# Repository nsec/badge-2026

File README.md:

# NorthSec Badge 2026 Firmware (ESP32-S3)

Bare-bones firmware scaffold for the **NorthSec 2026 CTF badge**, targeting **ESP32-S3**.

Design goals (repo requirements):

- **Arduino framework**, but **no `.ino`** (pure C++ entrypoint)
- **PlatformIO-based** build (produces flashable `.bin` outputs)
- **Two concurrent firmware images** via partitions: **`conference`** and **`ctf`**
- A simple **serial CLI**, including a command to **switch which firmware boots next**
- Clear hierarchy separating:
  - `lib/core/` → hardware/system modules
  - `lib/challenges/` → CTF challenge modules
- GitHub Actions workflow builds on PR/push to `main`, and **publishes artifacts on version tags**

## Repo layout

```
src/
  main.cpp                     C++ Arduino entrypoint (no .ino)

lib/
  core/
    cli/                        Serial command line
    system/                     OTA boot selection / dual-firmware helpers
    hardware/                   Hardware abstraction (pins, drivers)
  challenges/
    registry.*                  Challenge init/tick hooks
    example_challenge.*         Placeholder challenge module

partitions/
  badge_factory_ota.csv         Partition table (conference + ctf)

.github/workflows/
  build.yml                     CI build + tag-based release

platformio.ini                  PlatformIO project config
```

## PlatformIO + Arduino (no .ino)

This project uses PlatformIO with the Arduino framework.
The entrypoint is `src/main.cpp` (standard Arduino `setup()` / `loop()`), not a `.ino`.

## Dual firmware: `conference` + `ctf`

The partition table `partitions/badge_factory_ota.csv` defines:

- `conference` (app) — a "golden" image
- `ctf` (app) — an alternate/updated image
- `otadata` (data) — controls which app partition boots next

### How switching works

Under Arduino-ESP32, you can call ESP-IDF’s OTA APIs. This repo wraps them in:

- `lib/core/system/ota_manager.*`

That module provides:

- `core::ota::printBootInfo(Stream&)`
- `core::ota::setNextBoot(BootTarget, Stream&)`

## Serial CLI

The CLI is implemented in `lib/core/cli/` and runs over `Serial` at **115200**.

Commands:

- `help`
- `info` — print running partition and configured boot partition
- `boot conference` — set *next boot* to `conference` and reboot
- `boot ctf` — set *next boot* to `ctf` and reboot
- `reboot`

## Building locally

### Prerequisites

- **VS Code** with **PlatformIO IDE extension** installed, **OR**
- **PlatformIO Core** (CLI) installed

### Windows Setup (Important!)

**This project uses ESP-IDF framework to avoid Windows path-length issues with Arduino-ESP32 SDK extraction.**

Before building, set a short PlatformIO core directory to prevent path issues:

```powershell
# Set environment variable permanently (restart VS Code after)
setx PLATFORMIO_CORE_DIR C:\pio
```

Then **restart VS Code** or your terminal.

### First-Time Setup

1. Clone this repository:
   ```powershell
   git clone https://github.com/yourusername/badge-2026.git
   cd badge-2026
   ```

2. Set the short core directory (Windows only, see above)

3. Open the project in VS Code with PlatformIO extension, or use CLI

### Build

**In VS Code:** Click the PlatformIO "Build" button (checkmark icon) in the bottom toolbar

**Or via CLI:**
```powershell
# Build for conference partition (default)
C:\pio\penv\Scripts\platformio.exe run -e esp32-s3-devkitc-1-conference

# Or if platformio is in PATH
pio run
```

First build will download Arduino-ESP32 framework and toolchains. Subsequent builds are much faster.

### Dual Firmware Build

The badge uses a **conference + CTF** partition layout for dual-firmware boot:

- **conference** partition (`0x10000`) - Conference/stable image
- **ctf** partition (`0x150000`) - CTF challenges image

**To flash both partitions:**

```powershell
# 1. Upload to conference partition
C:\pio\penv\Scripts\platformio.exe run -e esp32-s3-devkitc-1-conference -t upload

# 2. Upload the CTF firmware to ctf partition
C:\pio\penv\Scripts\platformio.exe run -e esp32-s3-devkitc-1-ctf -t upload
```

**In VS Code:** Use the environment switcher in the bottom toolbar to select `esp32-s3-devkitc-1-conference` or `esp32-s3-devkitc-1-ctf`, then click Upload.

After flashing both, you can use the badge CLI commands to switch between them:
- `boot conference` - Set next boot to conference partition
- `boot ctf` - Set next boot to ctf partition
- `info` - Show current boot partition

Build outputs (including flashable binaries) appear under:

- `.pio/build/<env>/firmware.bin`
- `.pio/build/<env>/bootloader.bin`
- `.pio/build/<env>/partitions.bin`

### Flash

If you have a board connected and the correct upload port set:

```powershell
pio run -t upload
```

### Monitor

```powershell
pio device monitor
```

## Native Simulator

A desktop simulator allows running the badge firmware on your development machine
without hardware. Useful for testing CLI commands, debugging, and development.

### Prerequisites

- PlatformIO Core (CLI)
- GCC with C++17 and pthread support (Linux/macOS)
- For Windows: WSL recommended

### First-Time Setup

Initialize the FreeRTOS submodule:

```bash
git submodule update --init --recursive
```

### Build

```bash
pio run -e native
```

### Run

```bash
./.pio/build/native/program
```

The simulator presents the same CLI as the real badge. Press `Ctrl+C` to exit.

## CI/CD - GitHub Actions Workflow

### Automated Builds

The workflow in `.github/workflows/build.yml` automatically builds firmware on:

- **Pull Requests** targeting `main` - Build verification
- **Push to `main`** - Build and upload artifacts
- **Version Tags** (`v*`) - Build, create GitHub Release with binaries

### What Gets Built

Both firmware variants are built in parallel:
- **Conference firmware** (`badge-conference.bin`) - Conference mode with schedule and social features
- **CTF firmware** (`badge-ctf.bin`) - CTF challenges mode
- Supporting files: `bootloader.bin`, `partitions.bin`

### Creating a Release

**Step 1: Open a Pull Request**
```bash
git checkout -b feature-my-changes
# Make your changes
git add .
git commit -m "Add new feature"
git push origin feature-my-changes
```
Open PR on GitHub targeting `main` branch. GitHub Actions will build and verify.

**Step 2: Merge to Main**
After review, merge the PR. This triggers a build and uploads artifacts.

**Step 3: Create a Release Tag**
```bash
# Pull latest main
git checkout main
git pull origin main

# Create and push version tag
git tag v1.0.0
git push origin v1.0.0
```

Or use GitHub's web interface:
1. Go to repository → Releases → "Create a new release"
2. Click "Choose a tag" → Type new tag (e.g., `v1.0.0`) → "Create new tag"
3. Set release title (e.g., "NorthSec Badge 2026 v1.0.0")
4. GitHub Actions will automatically build and attach binaries

### Release Artifacts

Each release includes:
- `badge-conference.bin` - Conference firmware for conference partition
- `badge-ctf.bin` - CTF challenges firmware for CTF partition
- `bootloader.bin` - ESP32-S3 bootloader
- `partitions.bin` - Partition table
- `FLASH_INSTRUCTIONS.txt` - Complete flashing guide

## Flashing Pre-Built Firmware

### Prerequisites

Install esptool:
```bash
pip install esptool
```

Find your serial port:
- **Windows**: Check Device Manager → Ports (COM & LPT) → Look for "USB Serial Device" (e.g., COM4)
- **Linux**: `ls /dev/ttyACM* /dev/ttyUSB*` (usually /dev/ttyACM0)
- **Mac**: `ls /dev/cu.*` (look for cu.usbmodem*)

### Download Release Files

Go to [Releases](https://github.com/yourusername/badge-2026/releases) and download the latest `.zip` or individual files.

### Flash All (Recommended for New Badges)

Flash bootloader, partition table, and both firmware images:

**Windows:**
```powershell
python -m esptool --chip esp32s3 --port COM4 --baud 460800 ^
  --before default_reset --after hard_reset write_flash -z ^
  --flash_mode dio --flash_freq 80m --flash_size 8MB ^
  0x0 bootloader.bin ^
  0x8000 partitions.bin ^
  0x10000 badge-conference.bin ^
  0x150000 badge-ctf.bin
```

**Linux/Mac:**
```bash
python3 -m esptool --chip esp32s3 --port /dev/ttyACM0 --baud 460800 \
  --before default_reset --after hard_reset write_flash -z \
  --flash_mode dio --flash_freq 80m --flash_size 8MB \
  0x0 bootloader.bin \
  0x8000 partitions.bin \
  0x10000 badge-conference.bin \
  0x150000 badge-ctf.bin
```

### Update Only Firmware (Keep Existing Bootloader/Partitions)

If badges are already initialized, flash only updated firmware:

**Conference firmware only:**
```bash
python -m esptool --chip esp32s3 --port <PORT> --baud 460800 \
  write_flash -z 0x10000 badge-conference.bin
```

**CTF firmware only:**
```bash
python -m esptool --chip esp32s3 --port <PORT> --baud 460800 \
  write_flash -z 0x150000 badge-ctf.bin
```

**Both firmwares:**
```bash
python -m esptool --chip esp32s3 --port <PORT> --baud 460800 \
  write_flash -z 0x10000 badge-conference.bin 0x150000 badge-ctf.bin
```

### Verify Flash

Connect to serial console at 115200 baud:
```bash
# Windows
python -m serial.tools.miniterm COM4 115200

# Linux/Mac
python3 -m serial.tools.miniterm /dev/ttyACM0 115200
```

You should see the boot banner and CLI prompt. Type `help` to see available commands.

### Switch Between Firmwares

At the CLI prompt:
- `boot conference` - Reboot to conference firmware
- `boot ctf` - Reboot to CTF challenges firmware
- `info` - Show current running partition

## Additional Documentation

- **[FLASHING.md](FLASHING.md)** - Complete flashing guide for mass production and distribution
- **[CONTRIBUTING.md](CONTRIBUTING.md)** - Developer guide for adding features and challenges
- **[.github/workflows/build.yml](.github/workflows/build.yml)** - CI/CD configuration reference

## Firmware Architecture

### Dual-Firmware Design

This badge uses a unique dual-firmware architecture:

- **Conference Partition (0x10000)** - Conference mode
  - Boots by default on new badges
  - Contains conference-specific features (schedule, social, etc.)
  - Libraries: `core` + `conference`
  
- **CTF Partition (0x150000)** - CTF Challenges mode
  - Accessible via `boot ctf` command
  - Contains competition challenges (crypto, hardware, etc.)
  - Libraries: `core` + `challenges`

Both firmwares share the `core` library (CLI, OTA management, hardware abstraction) but have completely different feature sets.

### Adding New Features

See [CONTRIBUTING.md](CONTRIBUTING.md) for detailed instructions on adding:
- Conference modules (conference firmware)
- Challenge modules (CTF firmware)
- Core utilities (shared by both)

## License

Apache-2.0 (see `LICENSE`).

## Credits
NorthSec CTF badge 2026 is brought to you by the teamwork of:

 - [20th](https://github.com/20th)
 - [Svieg](https://github.com/Svieg)
 - [TheKGBSpy](https://github.com/TheKGBSpy)
 - [jgalar](https://github.com/jgalar)
 - [lle](https://github.com/lle)
 - [mjeanson](https://github.com/mjeanson)
 - [nyx0](https://github.com/nyx0)
 - [p0ns](https://github.com/p0ns)
 - [padraignix](https://github.com/padraignix)

Special thanks to:
 - [Marc-Olivier](https://github.com/D3c4f-NS)
 - David

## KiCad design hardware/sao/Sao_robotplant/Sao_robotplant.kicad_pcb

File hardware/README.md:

This folder contains the design files of the NorthSec 2026 badge.

## Folder structure

| Folder     | Content                                           |
|:-----------|:--------------------------------------------------|
| boards     | Kicad schematics & pcb layout                     |
| datasheets | datasheets of used electrical components          |
| mechanical | Full FreeCAD 3d model of all components of flower |

## Schematic

**Interactive schematic:**

- [Open Badge schematics in KiCanvas](https://kicanvas.org/?repo=https%3A%2F%2Fgithub.com%2Fnsec%2Fbadge-2026%2Ftree%2Fmain%2Fhardware%2Fbadge)
- [Open Sun SAO schematics in KiCanvas](https://kicanvas.org/?repo=https%3A%2F%2Fgithub.com%2Fnsec%2Fbadge-2026%2Ftree%2Fmain%2Fhardware%2Fsao%2FSao_SUN)
- [Open Tree SAO schematics in KiCanvas](https://kicanvas.org/?repo=https%3A%2F%2Fgithub.com%2Fnsec%2Fbadge-2026%2Ftree%2Fmain%2Fhardware%2Fsao%2FSao_Tree)
- [Open Robotplant SAO schematics in KiCanvas](https://kicanvas.org/?repo=https%3A%2F%2Fgithub.com%2Fnsec%2Fbadge-2026%2Ftree%2Fmain%2Fhardware%2Fsao%2FSao_robotplant)

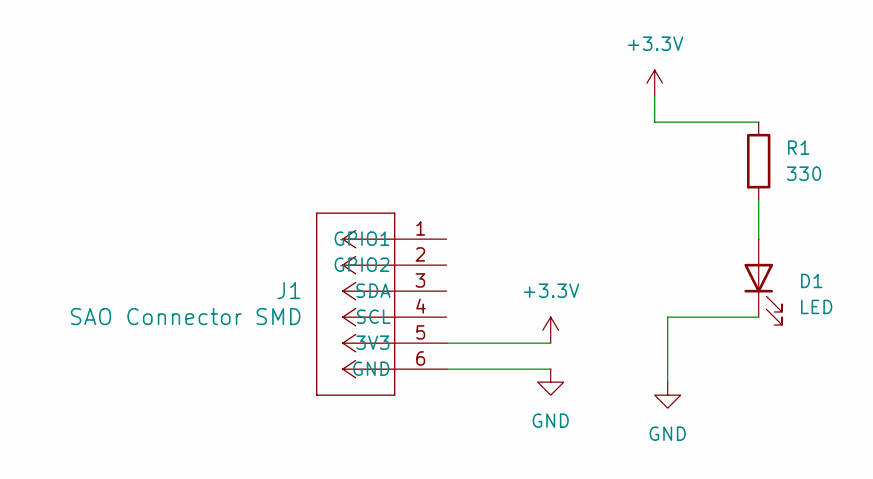
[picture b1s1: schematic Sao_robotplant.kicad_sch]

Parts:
D1: LED; LED_D3.0mm
J1: SAO Connector SMD
R1: 330; R_Axial_DIN0204_L3.6mm_D1.6mm_P7.62mm_Horizontal

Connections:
+3.3V: J1.5 (3V3), R1.1
GND: D1.1 (K), J1.6 (GND)
unnamed: D1.2 (A), R1.2

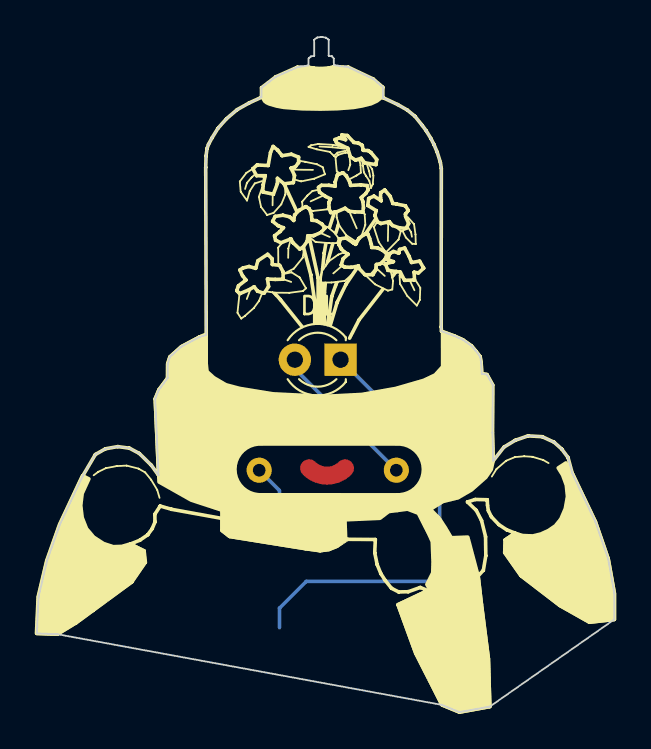
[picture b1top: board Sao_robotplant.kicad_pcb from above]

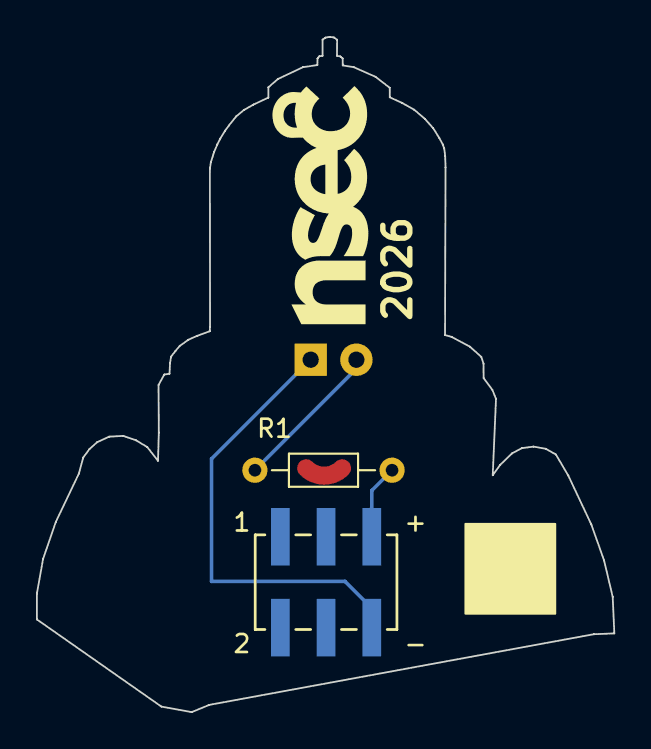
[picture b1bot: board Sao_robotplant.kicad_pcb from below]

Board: 2 copper layers, 32.1 x 37.5 mm, 3 parts (2 on the bottom side), 3 nets.

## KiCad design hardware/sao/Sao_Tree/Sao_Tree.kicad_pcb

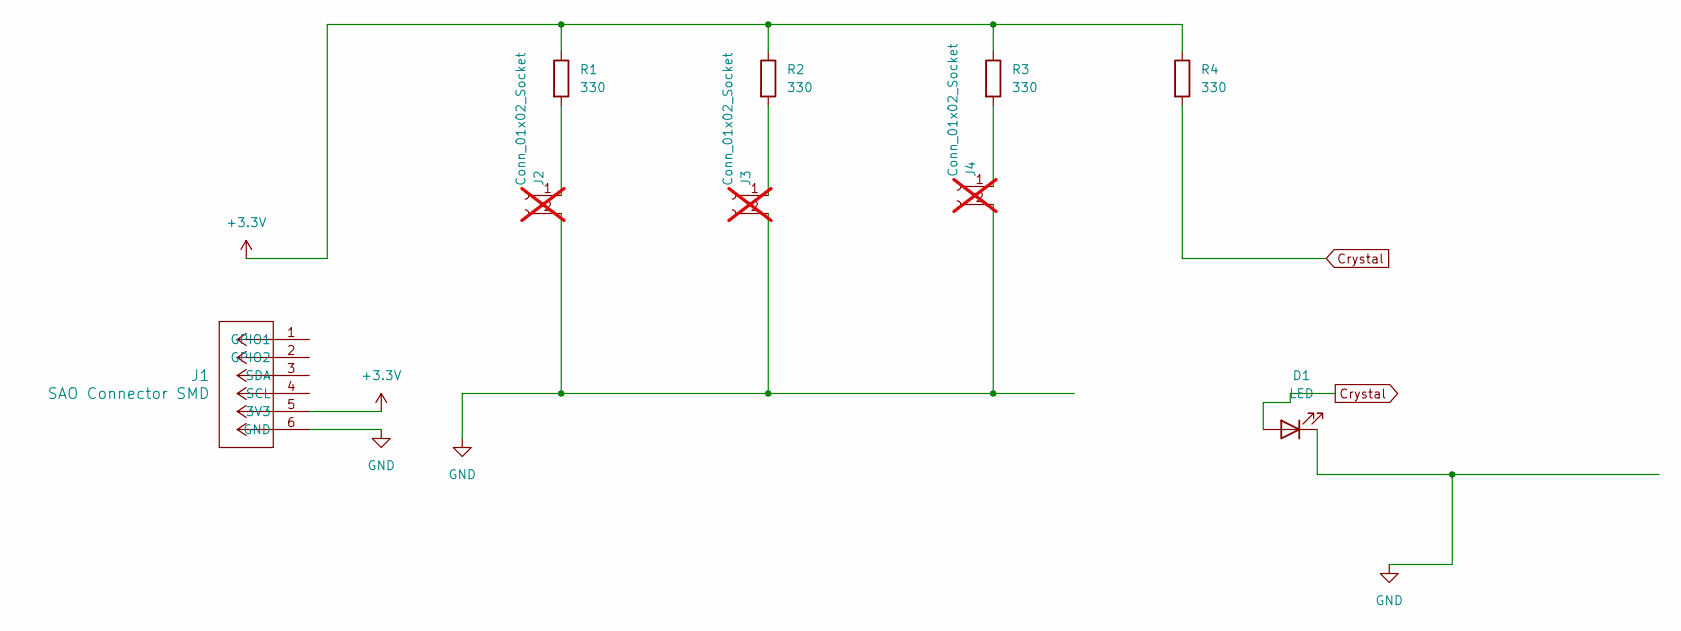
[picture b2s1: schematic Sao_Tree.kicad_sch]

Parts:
D1: LED; LED_1206_3216Metric
J1: SAO Connector SMD
J2, J3, J4: Conn_01x02_Socket; PinSocket_1x02_P2.00mm_Vertical; not fitted
R1, R2, R3, R4: 330; R_Axial_DIN0204_L3.6mm_D1.6mm_P7.62mm_Horizontal

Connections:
+3.3V: J1.5 (3V3), R1.1, R2.1, R3.1, R4.1
Crystal: D1.2 (A), R4.2
GND: D1.1 (K), J1.6 (GND), J2.2, J3.2, J4.2
unnamed: J2.1, R1.2
unnamed: J3.1, R2.2
unnamed: J4.1, R3.2

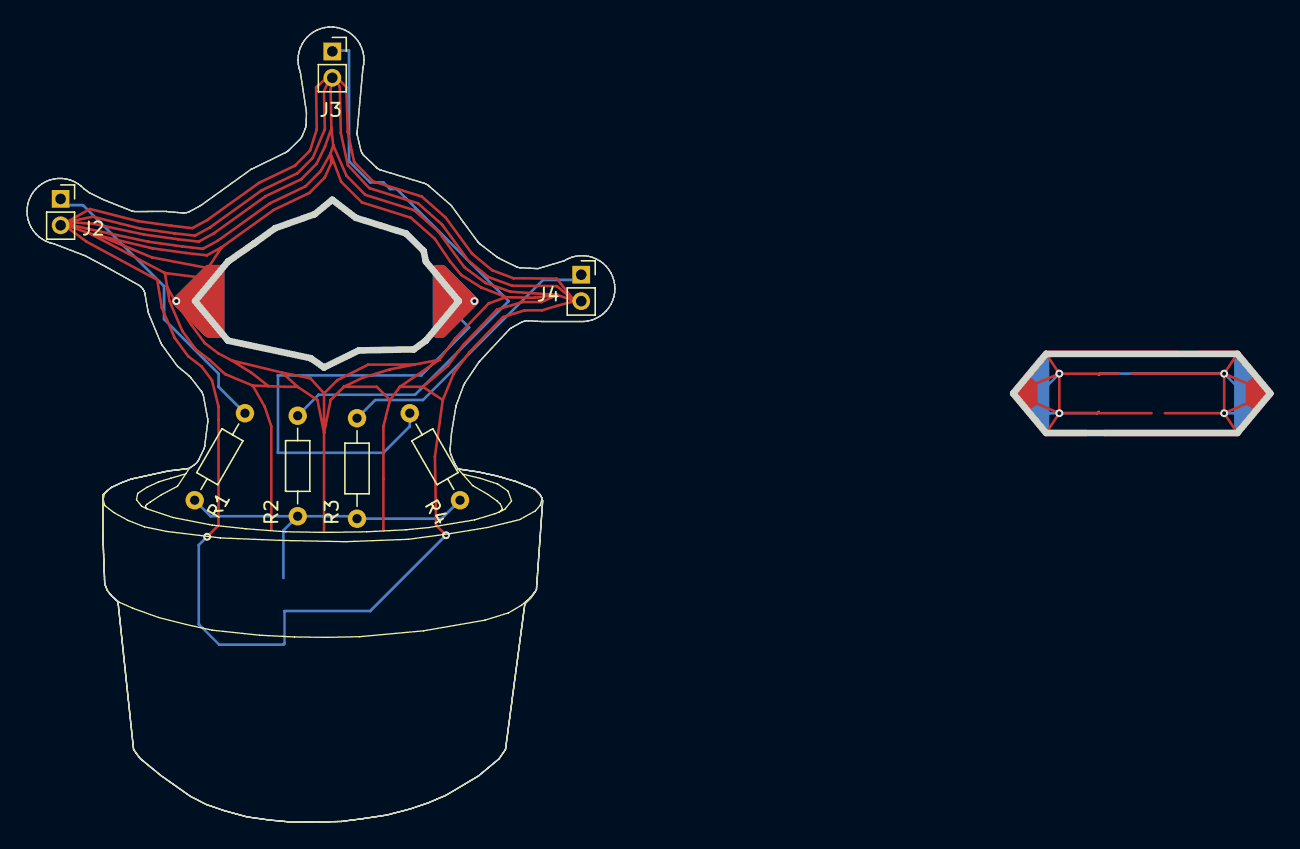
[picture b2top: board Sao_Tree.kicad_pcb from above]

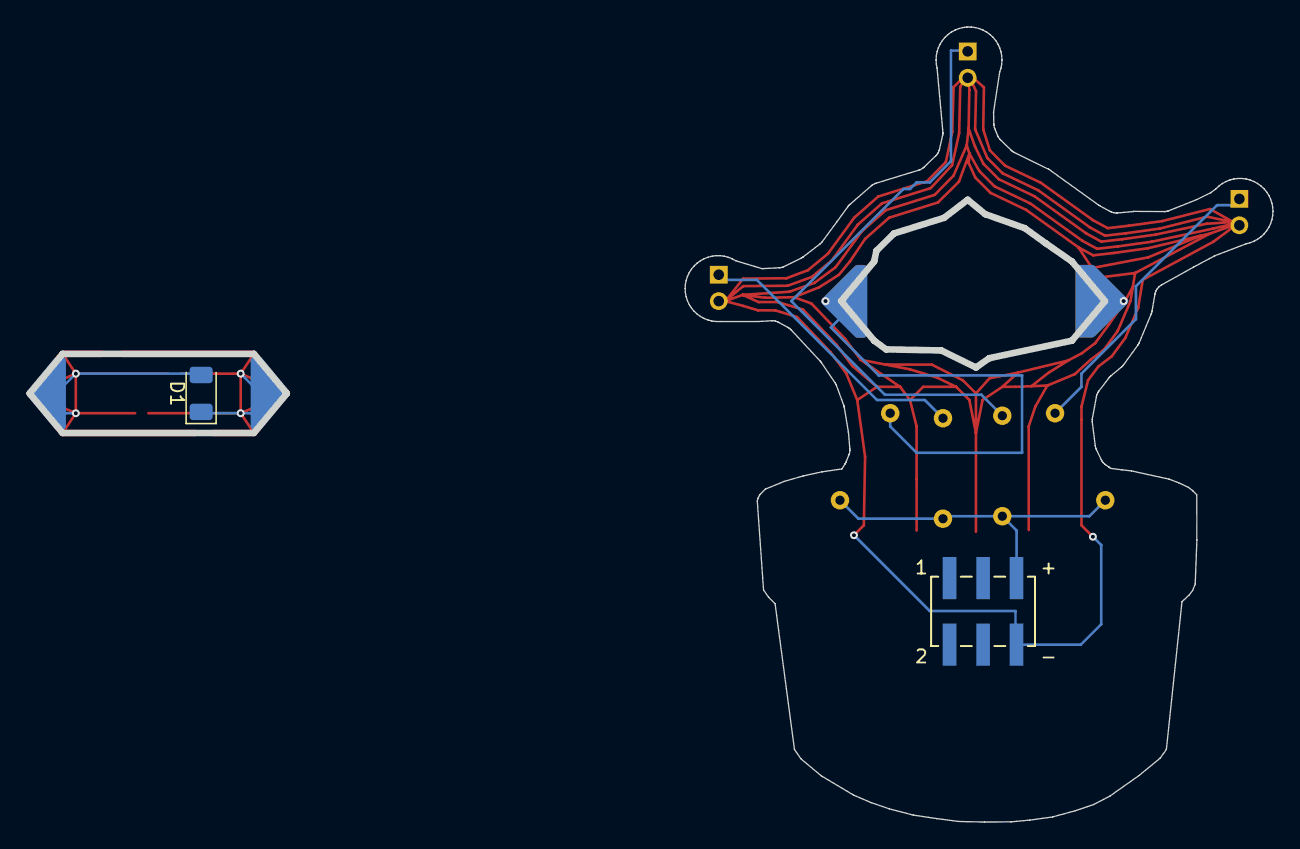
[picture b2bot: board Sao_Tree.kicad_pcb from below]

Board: 2 copper layers, 44.6 x 60.3 mm, 11 parts (2 on the bottom side), 6 nets.

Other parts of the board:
B1, B2: Board

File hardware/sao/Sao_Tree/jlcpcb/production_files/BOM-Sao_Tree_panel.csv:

Comment,Designator,Footprint,LCSC,Quantity
LED,D1,LED_1206_3216Metric,,1
Conn_01x02_Socket,,PinSocket_1x02_P2.00mm_Vertical,,0
330,R4,R_Axial_DIN0204_L3.6mm_D1.6mm_P7.62mm_Horizontal,,1
Conn_01x02_Socket,,PinSocket_1x02_P2.00mm_Vertical,,0
330,R1,R_Axial_DIN0204_L3.6mm_D1.6mm_P7.62mm_Horizontal,,1
Conn_01x02_Socket,,PinSocket_1x02_P2.00mm_Vertical,,0
330,R3,R_Axial_DIN0204_L3.6mm_D1.6mm_P7.62mm_Horizontal,,1
330,R2,R_Axial_DIN0204_L3.6mm_D1.6mm_P7.62mm_Horizontal,,1
SAO Connector SMD,J1,SAO Connector SMD,,1

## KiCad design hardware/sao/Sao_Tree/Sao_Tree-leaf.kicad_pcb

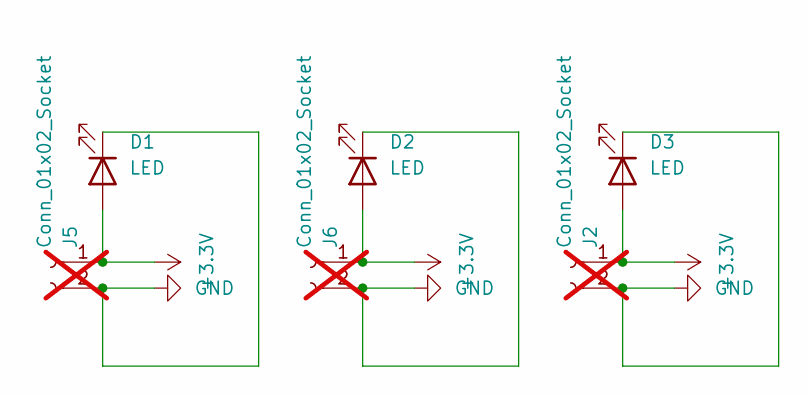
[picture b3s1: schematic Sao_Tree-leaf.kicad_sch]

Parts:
D1: LED; LED_1206_3216Metric
D2: LED; LED_D5.0mm
D3: LED; LED_0805_2012Metric
J2, J5, J6: Conn_01x02_Socket; PinSocket_1x02_P2.00mm_Vertical; not fitted

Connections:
+3.3V: D1.2 (A), D2.2 (A), D3.2 (A), J2.1, J5.1, J6.1
GND: D1.1 (K), D2.1 (K), D3.1 (K), J2.2, J5.2, J6.2

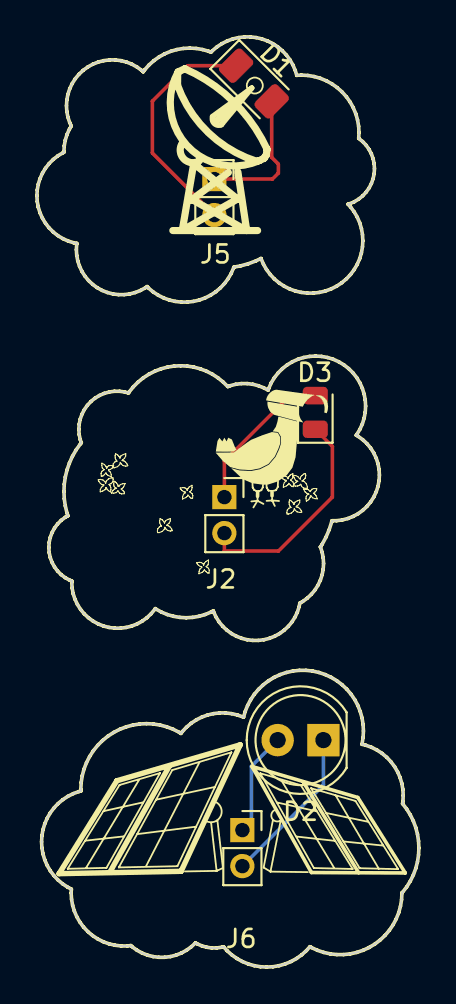
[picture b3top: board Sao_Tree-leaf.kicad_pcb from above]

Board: 2 copper layers, 21.2 x 51.7 mm, 9 parts (0 on the bottom side), 2 nets.

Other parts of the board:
B1, B2, B3: Board

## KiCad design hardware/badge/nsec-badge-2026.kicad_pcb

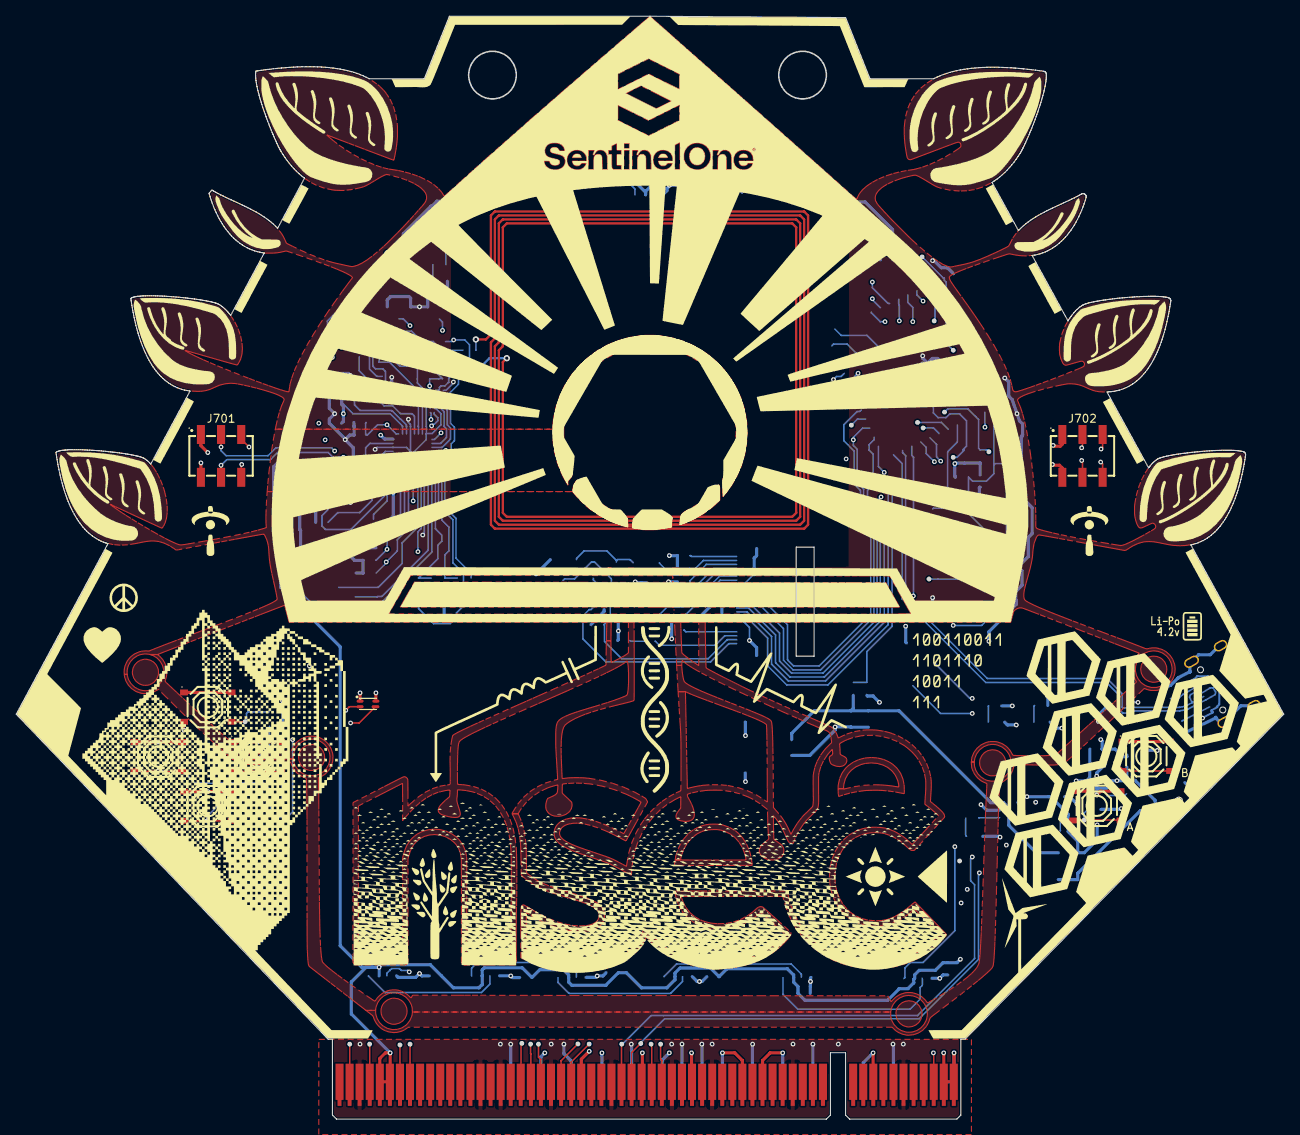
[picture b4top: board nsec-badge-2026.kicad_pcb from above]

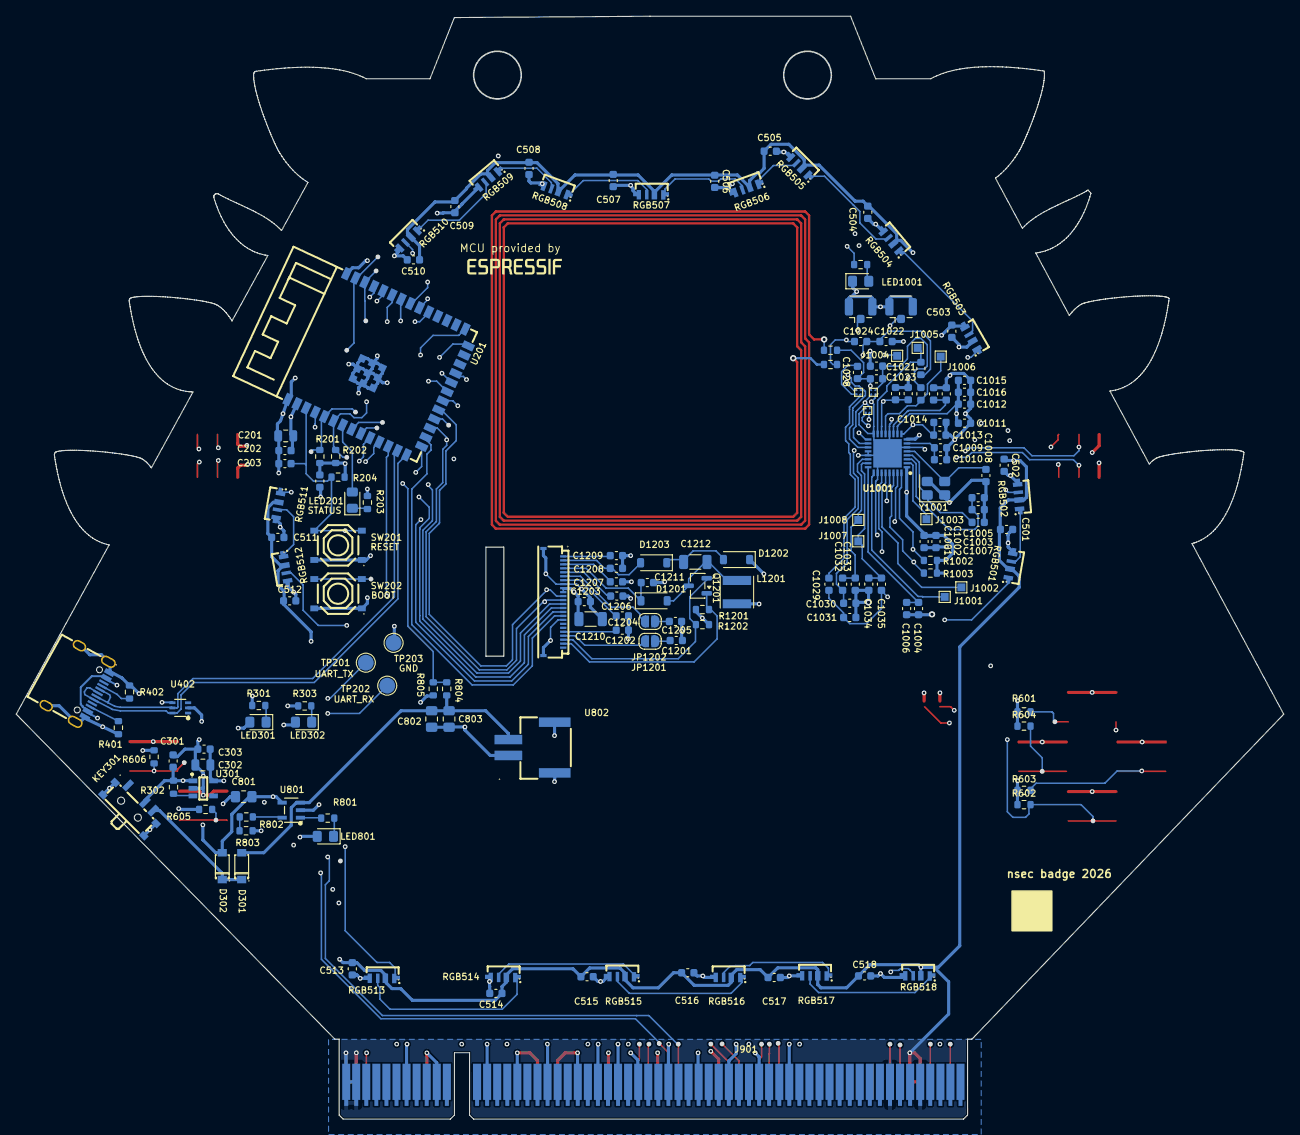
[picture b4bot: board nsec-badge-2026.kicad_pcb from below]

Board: 4 copper layers, 159.8 x 139.1 mm, 171 parts (161 on the bottom side), 106 nets.

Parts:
C201, C302: 10uF; C_0805_2012Metric
C202, C501, C502, C503, C504, C505, C506, C507, C508, C509, C510, C511, C512, C513, C514, C515, C516, C517, C518, C1101: 0.1uF; C_0603_1608Metric
C203, C301, C303, C1004, C1201, C1202, C1203, C1204, C1205, C1206, C1207, C1208, C1209, C1211: 1uF; C_0603_1608Metric
C801: 4.7uF; C_0805_2012Metric_Pad1.18x1.45mm_HandSolder
C802: 10uF; C_0805_2012Metric_Pad1.18x1.45mm_HandSolder
C803: 1uF; C_0805_2012Metric_Pad1.18x1.45mm_HandSolder
C1001, C1003, C1006, C1009, C1011, C1013, C1015, C1019: 10nF; C_0603_1608Metric
C1002, C1005, C1010, C1012, C1014, C1016: 2u2F; C_0603_1608Metric
C1007, C1008: 12pF; C_0603_1608Metric
C1017: 1nF; C_0603_1608Metric
C1018: 22nF; C_0603_1608Metric
C1020: 4u7F; C_0603_1608Metric
C1021, C1022: 680pF; C_0603_1608Metric
C1023, C1024: 33pF; C_0603_1608Metric
C1025, C1026, C1027: LXRW0YV600-054; X2SON-4_L0.6-W0.6-P0.40-BL
C1028, C1029: 150pF; C_0603_1608Metric
C1030, C1031: 47pF; C_0603_1608Metric
C1032, C1035: 10pF; C_0603_1608Metric
C1033, C1034: 220pF; C_0603_1608Metric
C1210, C1212: 4.7uF/50V; C_1206_3216Metric
D301, D302: MBR120LSF; SOD-123_L2.8-W1.8-LS3.7-RD
D1201, D1202, D1203: MBR0530; D_SOD-123
J701, J702: PM254-2-03-S-8_5; HDR-SMD_6P-P2.54-V-F-R2-C3-LS7.0
J901: Bus_PCI_32bit_Universal; BUS_PCI
J1001, J1002, J1003, J1004, J1005, J1006, J1007, J1008: Conn_01x01_Female; TestPoint_Pad_1.0x1.0mm
JP1201, JP1202: Jumper_2_Open; SolderJumper-2_P1.3mm_Open_RoundedPad1.0x1.5mm
KEY301: SSSS811101; SW-SMD_SSSS811101
L1001, L1002: MLJ1608WR27JT000; L_0603_1608Metric
L1201: 10uH; L_Vishay_IFSC-1515AH_4x4x1.8mm
LED201, LED301, LED302, LED801, LED1001: NCD0805R1; LED_0805_2012Metric_Pad1.15x1.40mm_HandSolder
P1001, P1002: U.FL-R-SMT-1_10_; U.FL_Hirose_U.FL-R-SMT-1_Vertical
Q1201: IRLML0100TRPBF; SOT-23-3
R201, R202, R204, R601, R602, R603, R604, R605, R606, R1201: 10K; R_0603_1608Metric
R203, R801, R802, R803, R1001: 1K; R_0603_1608Metric
R301, R303, R401, R402: 5.1K; R_0603_1608Metric
R302, R805: 100K; R_0603_1608Metric
R804: 390K; R_0603_1608Metric
R1002, R1003: 1k8 NF; R_0603_1608Metric
R1004, R1005: 1R5; R_0603_1608Metric
R1202: 0.47; R_0603_1608Metric
RGB501, RGB502, RGB503, RGB504, RGB505, RGB506, RGB507, RGB508, RGB509, RGB510, RGB511, RGB512, RGB513, RGB514, RGB515, RGB516, RGB517, RGB518: SK6812SIDE-A_C5378721; LED-SMD_SK6812SIDE-A_C5378721
SW201, SW202, SW601, SW602, SW603, SW604, SW605, SW606: TS-1187A-C-C-B; SW-SMD_4P-L5.1-W5.1-P3.70-LS6.5-TL_H1.5
TP201: UART_TX; TestPoint_Pad_D2.0mm
TP202: UART_RX; TestPoint_Pad_D2.0mm
TP203: GND; TestPoint_Pad_D2.0mm
U201: ESP32-S3-WROOM-1(N16R8); WIRELM-SMD_ESP32-S3-WROOM-1
U301: AP2112K-3_3TRG1; SOT-25-5_L2.9-W1.6-P0.95-LS2.8-BL
U401: TYPE-C-31-M-12; USB-C_SMD-TYPE-C-31-M-12
U402: TPSMF05CT1G; SOT-363_L2.0-W1.3-P0.65-LS2.1-BL
U801: XT4054K421MR-G; SOT-23-5_L3.0-W1.7-P0.95-LS2.8-BL
U802: XDWF-0920-02P; CONN-SMD_XDWF-0920-02P
U1001: ST25R3916-AQWT; QFN50P500X500X100-33N-D
U1101: VEML6040A3OG; SENSOR_SMD_VEML6040A3OG
U1202: HC-FPC-05-09-24RLTAG; FPC-SMD_24P-P0.50_HC-FPC-05-09-24RLTAG
Y1001: 27.12Mhz; Crystal_SMD_3225-4Pin_3.2x2.5mm

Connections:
+3V3: C201.1, C202.1, C302.1, C303.1, C1001.1, C1002.1, C1011.1, C1012.1, C1015.1, C1016.1, C1101.1, C1203.2, C1210.1, J701.1, J702.1, J901.A21 (+3.3V), J901.A27 (+3.3V), J901.A33 (+3.3V), J901.A39 (+3.3V), J901.A45 (+3.3V), J901.A53 (+3.3V), J901.B25 (+3.3V), J901.B31 (+3.3V), J901.B36 (+3.3V), J901.B41 (+3.3V), J901.B43 (+3.3V), J901.B54 (+3.3V), L1201.1, LED302.2 (A), R201.1, R202.1, R204.1, R601.1, R602.1, R603.1, R604.1, R605.1, R606.1, R1002.1, R1003.1, U201.2 (3V3), U301.5 (VOUT), U1001.1 (VDD_IO), U1001.8 (VDD), U1001.10 (VDD_TX), U1101.4 (VDD), U1202.15, U1202.16
/BTN_DOWN: J901.B4 (TDO), R602.2, SW602.3 (C), SW602.4 (D), U201.22 (IO14)
/BTN_UP: J901.B2 (TCK), R601.2, SW601.3 (C), SW601.4 (D), U201.21 (IO13)
/Battery Charger/CHRG: R801.2, U801.1 (CHRG#)
/Battery Charger/RPROG: R802.1, U801.5 (PROG)
/Battery Charger/VBAT_DIV: R804.2, R805.1, U201.4 (IO4)
/Buttons/BTN_A: R605.2, SW605.3 (C), SW605.4 (D), U201.10 (IO17)
/Buttons/BTN_B: R606.2, SW606.3 (C), SW606.4 (D), U201.11 (IO18)
/Buttons/BTN_LEFT: R603.2, SW603.3 (C), SW603.4 (D), U201.8 (IO15)
/Buttons/BTN_RIGHT: R604.2, SW604.3 (C), SW604.4 (D), U201.9 (IO16)
/ESP32-S3/BOOTSEL: J901.B30 (AD[19]), SW202.3 (C), SW202.4 (D), U201.27 (IO0)
/ESP32-S3/GPIO12: U201.20 (IO12), U1001.29 (BSS)
/ESP32-S3/GPIO21: U201.23 (IO21), U1001.27 (IRQ)
/ESP32-S3/GPIO38: J901.B7 (~INTB#), U201.31 (IO38)
/ESP32-S3/GPIO39: J901.B8 (~INTD#), U201.32 (IO39)
/ESP32-S3/GPIO40: R1001.1, U201.33 (IO40)
/ESP32-S3/GPIO41: U201.34 (IO41), U1202.12
/ESP32-S3/GPIO42: U201.35 (IO42), U1202.11
/ESP32-S3/GPIO45: U201.26 (IO45), U1202.10
/ESP32-S3/GPIO46: U201.16 (IO46), U1202.9
/ESP32-S3/MCU_LED: LED201.2 (A), U201.7 (IO7)
/ESP32-S3/RESET: C203.1, J901.B29 (AD[21]), R204.2, SW201.3 (C), SW201.4 (D), U201.3 (EN)
/ESP32-S3/RGB_LED: RGB501.1 (DIN), U201.12 (IO8)
/ESP32-S3/UART_RX: J901.B24 (AD[25]), TP202.1, U201.36 (RXD0)
/ESP32-S3/UART_TX: J901.B23 (AD[27]), TP201.1, U201.37 (TXD0)
/ESP32-S3/USB_D+: U201.14 (IO20), U401.A6 (DP1), U401.B6 (DP2), U402.6
/ESP32-S3/USB_D-: U201.13 (IO19), U401.A7 (DN1), U401.B7 (DN2), U402.5
/GPIO1: J701.3, J702.3, J901.B19 (VIO), U201.39 (IO1)
/GPIO2: J701.4, J702.4, J901.B20 (AD[31]), U201.38 (IO2)
/GPIO3: J901.B21 (AD[29]), U201.15 (IO3)
/I2C_SCL: J701.5, J702.5, J901.B33 (~C/BE#[2]), R202.2, U201.6 (IO6), U1101.3 (SCL)
/I2C_SDA: J701.2, J702.2, J901.B32 (AD[17]), R201.2, U201.5 (IO5), U1101.2 (SDA)
/NFC/AAT_P: C1027.2 (VT), P1002.1 (In), U1001.19 (AAT_B)
/NFC/AAT_S: C1025.2 (VT), C1026.2 (VT), P1001.1 (In), U1001.18 (AAT_A)
/NFC/AGDC: C1004.1, C1006.1, U1001.24 (AGDC)
/NFC/EXT_LM: J1004.1, U1001.17 (EXT_LM)
/NFC/NFC_COIL: R1004.2, R1005.2
/NFC/RFI1: C1032.2, C1033.1, J1008.1, U1001.22 (RFI1)
/NFC/RFI2: C1034.2, C1035.1, J1007.1, U1001.23 (RFI2)
/NFC/RFO1: J1006.1, L1001.1, U1001.13 (RFO1)
/NFC/RFO2: J1005.1, L1002.1, U1001.15 (RFO2)
/NFC/VDD_A: C1009.1, C1010.1, U1001.7 (VDD_A)
/NFC/VDD_AM: C1017.1, C1018.1, U1001.11 (VDD_AM)
/NFC/VDD_D: C1003.1, C1005.1, U1001.3 (VDD_D)
/NFC/VDD_DR: C1013.1, C1014.1, C1019.1, C1020.1, U1001.9 (VDD_RF), U1001.14 (VDD_DR)
/Power Regulator/POWER_IN: D301.1 (C), D302.1 (C), KEY301.3
/RGB_END: J901.B60 (~ACK64#), RGB518.3 (DOUT)
/SPI_MISO: R1002.2, U201.18 (IO10), U1001.32 (MISO/SDA)
/SPI_MOSI: U201.19 (IO11), U1001.31 (MOSI), U1202.14
/SPI_SCK: R1003.2, U201.17 (IO9), U1001.30 (SCLK/SCL), U1202.13
/e-ink display/GDR: Q1201.1 (G), R1201.2, U1202.2
/e-ink display/PREVGH: C1211.1, D1201.1 (K), U1202.21
/e-ink display/PREVGL: C1208.2, D1203.2 (A), U1202.23
/e-ink display/RESE: Q1201.2 (S), R1202.2, U1202.3
/e-ink display/VCOM: C1209.2, U1202.24
/e-ink display/VDD: C1204.2, U1202.18
/e-ink display/VGH: C1202.2, U1202.5
/e-ink display/VGL: JP1201.2 (B), U1202.4
/e-ink display/VSH: C1206.2, U1202.20
/e-ink display/VSL: C1207.2, U1202.22
GND: C201.2, C202.2, C203.2, C301.2, C302.2, C303.2, C501.2, C502.2, C503.2, C504.2, C505.2, C506.2, C507.2, C508.2, C509.2, C510.2, C511.2, C512.2, C513.2, C514.2, C515.2, C516.2, C517.2, C518.2, C801.2, C802.2, C803.2, C1001.2, C1002.2, C1003.2, C1004.2, C1005.2, C1006.2, C1007.2, C1008.2, C1009.2, C1010.2, C1011.2, C1012.2, C1013.2, C1014.2, C1015.2, C1016.2, C1017.2, C1018.2, C1019.2, C1020.2, C1021.2, C1022.1, C1025.1 (G), C1026.1 (G), C1027.1 (G), C1030.2, C1031.1, C1033.2, C1034.1, C1101.2, C1201.1, C1202.1, C1203.1, C1204.1, C1205.1, C1206.1, C1207.1, C1208.1, C1209.1, C1210.2, C1211.2, D1202.1 (K), J701.6, J702.6, J901.A18 (GND), J901.A24 (GND), J901.A30 (GND), J901.A35 (GND), J901.A37 (GND), J901.A42 (GND), J901.A48 (GND), J901.A56 (GND), J901.B3 (GND), J901.B15 (GND), J901.B17 (GND), J901.B22 (GND), J901.B28 (GND), J901.B34 (GND), J901.B38 (GND), J901.B46 (GND), J901.B57 (GND), KEY301.4, KEY301.5, KEY301.6, KEY301.7, LED1001.1 (K), P1001.2 (Ext), P1002.2 (Ext), R203.2, R301.2, R303.2, R401.2, R402.2, R803.2, R805.2, R1201.1, R1202.1, RGB501.4 (GND), RGB502.4 (GND), RGB503.4 (GND), RGB504.4 (GND), RGB505.4 (GND), RGB506.4 (GND), RGB507.4 (GND), RGB508.4 (GND), RGB509.4 (GND), RGB510.4 (GND), RGB511.4 (GND), RGB512.4 (GND), RGB513.4 (GND), RGB514.4 (GND), RGB515.4 (GND), RGB516.4 (GND), RGB517.4 (GND), RGB518.4 (GND), SW201.1 (A), SW201.2 (B), SW202.1 (A), SW202.2 (B), SW601.1 (A), SW601.2 (B), SW602.1 (A), SW602.2 (B), SW603.1 (A), SW603.2 (B), SW604.1 (A), SW604.2 (B), SW605.1 (A), SW605.2 (B), SW606.1 (A), SW606.2 (B), TP203.1, U201.1 (GND), U201.40 (GND), U201.41 (GND), U301.2 (GND), U401.0 (SH), U401.1 (SH), U401.2 (SH), U401.3 (SH), U401.A1 (GND), U401.A12 (GND), U401.B1 (GND), U401.B12 (GND), U402.2, U801.2 (GND), U802.1, U802.3, U802.4, U1001.6 (GND_D), U1001.12 (GND_DR_1), U1001.16 (GND_DR_2), U1001.20 (I2C_EN), U1001.21 (VSS), U1001.26 (GND_A), U1001.33 (EP), U1101.1 (GND), U1202.8, U1202.17, U1202.25, U1202.26, Y1001.2, Y1001.4
unnamed: C1023.1, C1025.3 (Pt1), C1028.1, C1030.1, C1032.1, R1004.1
unnamed: C1021.1, C1023.2, C1025.4 (Pt2), L1001.2
unnamed: C1022.2, C1024.1, C1026.3 (Pt1), L1002.2
unnamed: C1024.2, C1026.4 (Pt2), C1029.2, C1031.2, C1035.2, R1005.1
unnamed: C1027.3 (Pt1), C1029.1
unnamed: C1027.4 (Pt2), C1028.2
unnamed: C1212.1, D1201.2 (A), L1201.2, Q1201.3 (D)
unnamed: C1212.2, D1202.2 (A), D1203.1 (K)
unnamed: C1201.2, JP1201.1 (A)
unnamed: C1205.2, JP1202.1 (A)
unnamed: JP1202.2 (B), U1202.19
unnamed: LED201.1 (K), R203.1
unnamed: LED301.1 (K), R301.1
unnamed: LED302.1 (K), R303.1
unnamed: LED801.1 (K), R801.1
unnamed: LED1001.2 (A), R1001.2
unnamed: R802.2, R803.1
unnamed: RGB501.3 (DOUT), RGB502.1 (DIN)
unnamed: RGB502.3 (DOUT), RGB503.1 (DIN)
unnamed: RGB503.3 (DOUT), RGB504.1 (DIN)
unnamed: RGB504.3 (DOUT), RGB505.1 (DIN)
unnamed: RGB505.3 (DOUT), RGB506.1 (DIN)
unnamed: RGB506.3 (DOUT), RGB507.1 (DIN)
unnamed: RGB507.3 (DOUT), RGB508.1 (DIN)
unnamed: RGB508.3 (DOUT), RGB509.1 (DIN)
unnamed: RGB509.3 (DOUT), RGB510.1 (DIN)
unnamed: RGB510.3 (DOUT), RGB511.1 (DIN)
unnamed: RGB511.3 (DOUT), RGB512.1 (DIN)
unnamed: RGB512.3 (DOUT), RGB513.1 (DIN)
unnamed: RGB513.3 (DOUT), RGB514.1 (DIN)
unnamed: RGB514.3 (DOUT), RGB515.1 (DIN)
unnamed: RGB515.3 (DOUT), RGB516.1 (DIN)
unnamed: RGB516.3 (DOUT), RGB517.1 (DIN)
unnamed: RGB517.3 (DOUT), RGB518.1 (DIN)
unnamed: R302.2, U301.3 (EN)
unnamed: R402.1, U401.A5 (CC1)
unnamed: R401.1, U401.B5 (CC2)
unnamed: J1002.1, U1001.28 (MCU_CLK)
unnamed: J1001.1, U1001.25 (TAD1)
unnamed: J1003.1, U1001.2 (TAD2)
unnamed: C1008.1, U1001.5 (XTI), Y1001.3
unnamed: C1007.1, U1001.4 (XTO), Y1001.1
VBAT: C802.1, C803.1, D301.2 (A), R804.1, U801.3 (BAT), U802.2
VBUS: C801.1, D302.2 (A), LED801.2 (A), U401.A4 (VBUS), U401.A9 (VBUS), U401.B4 (VBUS), U401.B9 (VBUS), U402.4, U801.4 (VCC)
VDD: C301.1, C501.1, C502.1, C503.1, C504.1, C505.1, C506.1, C507.1, C508.1, C509.1, C510.1, C511.1, C512.1, C513.1, C514.1, C515.1, C516.1, C517.1, C518.1, J901.A5 (+5V), J901.A8 (+5V), J901.A61 (+5V), J901.A62 (+5V), J901.B5 (+5V), J901.B6 (+5V), J901.B61 (+5V), J901.B62 (+5V), KEY301.2, LED301.2 (A), R302.1, RGB501.2 (VDD), RGB502.2 (VDD), RGB503.2 (VDD), RGB504.2 (VDD), RGB505.2 (VDD), RGB506.2 (VDD), RGB507.2 (VDD), RGB508.2 (VDD), RGB509.2 (VDD), RGB510.2 (VDD), RGB511.2 (VDD), RGB512.2 (VDD), RGB513.2 (VDD), RGB514.2 (VDD), RGB515.2 (VDD), RGB516.2 (VDD), RGB517.2 (VDD), RGB518.2 (VDD), U301.1 (VIN)

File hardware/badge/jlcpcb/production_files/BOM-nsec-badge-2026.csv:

Comment,Designator,Footprint,LCSC,Quantity
0.1uF,"C501,C502,C503,C504,C505,C506,C507,C508,C509,C510,C511,C512,C513,C514,C515,C516,C517,C518",C_0603_1608Metric,C14663,18
0.1uF,"C1101,C202",C_0603_1608Metric,C28233,2
0.47,R1202,R_0603_1608Metric,C23411,1
100K,R805,R_0603_1608Metric,C14675,1
100K,R302,R_0603_1608Metric,C25803,1
10K,"R201,R202,R204,R601,R602,R603,R604,R605,R606",R_0603_1608Metric,C25804,9
10nF,"C1001,C1003,C1006,C1009,C1011,C1013,C1015,C1019",C_0603_1608Metric,C57112,8
10pF,"C1032,C1035",C_0603_1608Metric,C1634,2
10uF,"C201,C302,C802",C_0805_2012Metric,C15850,3
10uH,L1201,L_Vishay_IFSC-1515AH_4x4x1.8mm,C222882,1
12pF,"C1007,C1008",C_0603_1608Metric,C38523,2
150pF,"C1028,C1029",C_0603_1608Metric,C1594,2
1K,R1001,R_0603_1608Metric,C14676,1
1K,"R203,R801,R802,R803",R_0603_1608Metric,C21190,4
1R5,"R1004,R1005",R_0603_1608Metric,C245932,2
1nF,C1017,C_0603_1608Metric,C1588,1
1uF,"C1004,C1201,C1202,C1203,C1204,C1205,C1206,C1207,C1208,C1209,C1211,C203,C301,C303",C_0603_1608Metric,C15849,14
1uF,C803,C_0805_2012Metric_Pad1.18x1.45mm_HandSolder,C28323,1
220pF,"C1033,C1034",C_0603_1608Metric,C1603,2
22nF,C1018,C_0603_1608Metric,C21122,1
27.12Mhz,Y1001,Crystal_SMD_3225-4Pin_3.2x2.5mm,C3003244,1
2u2F,"C1002,C1005,C1010,C1012,C1014,C1016",C_0603_1608Metric,C23630,6
33pF,"C1023,C1024",C_0603_1608Metric,C1663,2
390K,R804,R_0603_1608Metric,C23150,1
4.7uF,C801,C_0805_2012Metric_Pad1.18x1.45mm_HandSolder,C1779,1
4.7uF/50V,"C1210,C1212",C_1206_3216Metric,C29823,2
47pF,"C1030,C1031",C_0603_1608Metric,C1671,2
4u7F,C1020,C_0603_1608Metric,C19666,1
5.1K,"R301,R303,R401,R402",R_0603_1608Metric,C23186,4
680pF,"C1021,C1022",C_0603_1608Metric,C107055,2
AP2112K-3_3TRG1,U301,SOT-25-5_L2.9-W1.6-P0.95-LS2.8-BL,C47719,1
ESP32-S3-WROOM-1(N16R8),U201,WIRELM-SMD_ESP32-S3-WROOM-1,C2913202,1
HC-FPC-05-09-24RLTAG,U1202,FPC-SMD_24P-P0.50_HC-FPC-05-09-24RLTAG,C5213757,1
IRLML0100TRPBF,Q1201,SOT-23-3,C53658,1
LXRW0YV600-054,"C1025,C1026,C1027",X2SON-4_L0.6-W0.6-P0.40-BL,C2988749,3
MBR0530,"D1201,D1202,D1203",D_SOD-123,C77336,3
MBR120LSF,"D301,D302",SOD-123_L2.8-W1.8-LS3.7-RD,C130880,2
MLJ1608WR27JT000,"L1001,L1002",L_0603_1608Metric,C2041707,2
NCD0805R1,"LED1001,LED201,LED301,LED302,LED801",LED_0805_2012Metric_Pad1.15x1.40mm_HandSolder,C84256,5
PM254-2-03-S-8_5,"J701,J702",HDR-SMD_6P-P2.54-V-F-R2-C3-LS7.0,C3975148,2
SK6812SIDE-A_C5378721,"RGB501,RGB502,RGB503,RGB504,RGB505,RGB506,RGB507,RGB508,RGB509,RGB510,RGB511,RGB512,RGB513,RGB514,RGB515,RGB516,RGB517,RGB518",LED-SMD_SK6812SIDE-A_C5378721,C5378721,18
SSSS811101,KEY301,SW-SMD_SSSS811101,C109335,1
ST25R3916-AQWT,U1001,QFN50P500X500X100-33N-D,C2908147,1
TPSMF05CT1G,U402,SOT-363_L2.0-W1.3-P0.65-LS2.1-BL,C558443,1
TS-1187A-C-C-B,"SW201,SW202,SW601,SW602,SW603,SW604,SW605,SW606",SW-SMD_4P-L5.1-W5.1-P3.70-LS6.5-TL_H1.5,C318889,8
TYPE-C-31-M-12,U401,USB-C_SMD-TYPE-C-31-M-12,C165948,1
VEML6040A3OG,U1101,SENSOR_SMD_VEML6040A3OG,C78465,1
XDWF-0920-02P,U802,CONN-SMD_XDWF-0920-02P,C7527581,1
XT4054K421MR-G,U801,SOT-23-5_L3.0-W1.7-P0.95-LS2.8-BL,C141405,1
